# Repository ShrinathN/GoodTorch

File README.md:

# GoodTorch
An STM32G0 based torch for a 20W LED

# Summary
* STM32G0 MCU
* Boost converter (can operate in async or synchronous boost, depending on component placement)
* TP4056 based li-ion charging circuitry (1A max)
* USB-C for charging
* IR2104 gate driver (optional, if synchronous boost has to be used)

# Pics

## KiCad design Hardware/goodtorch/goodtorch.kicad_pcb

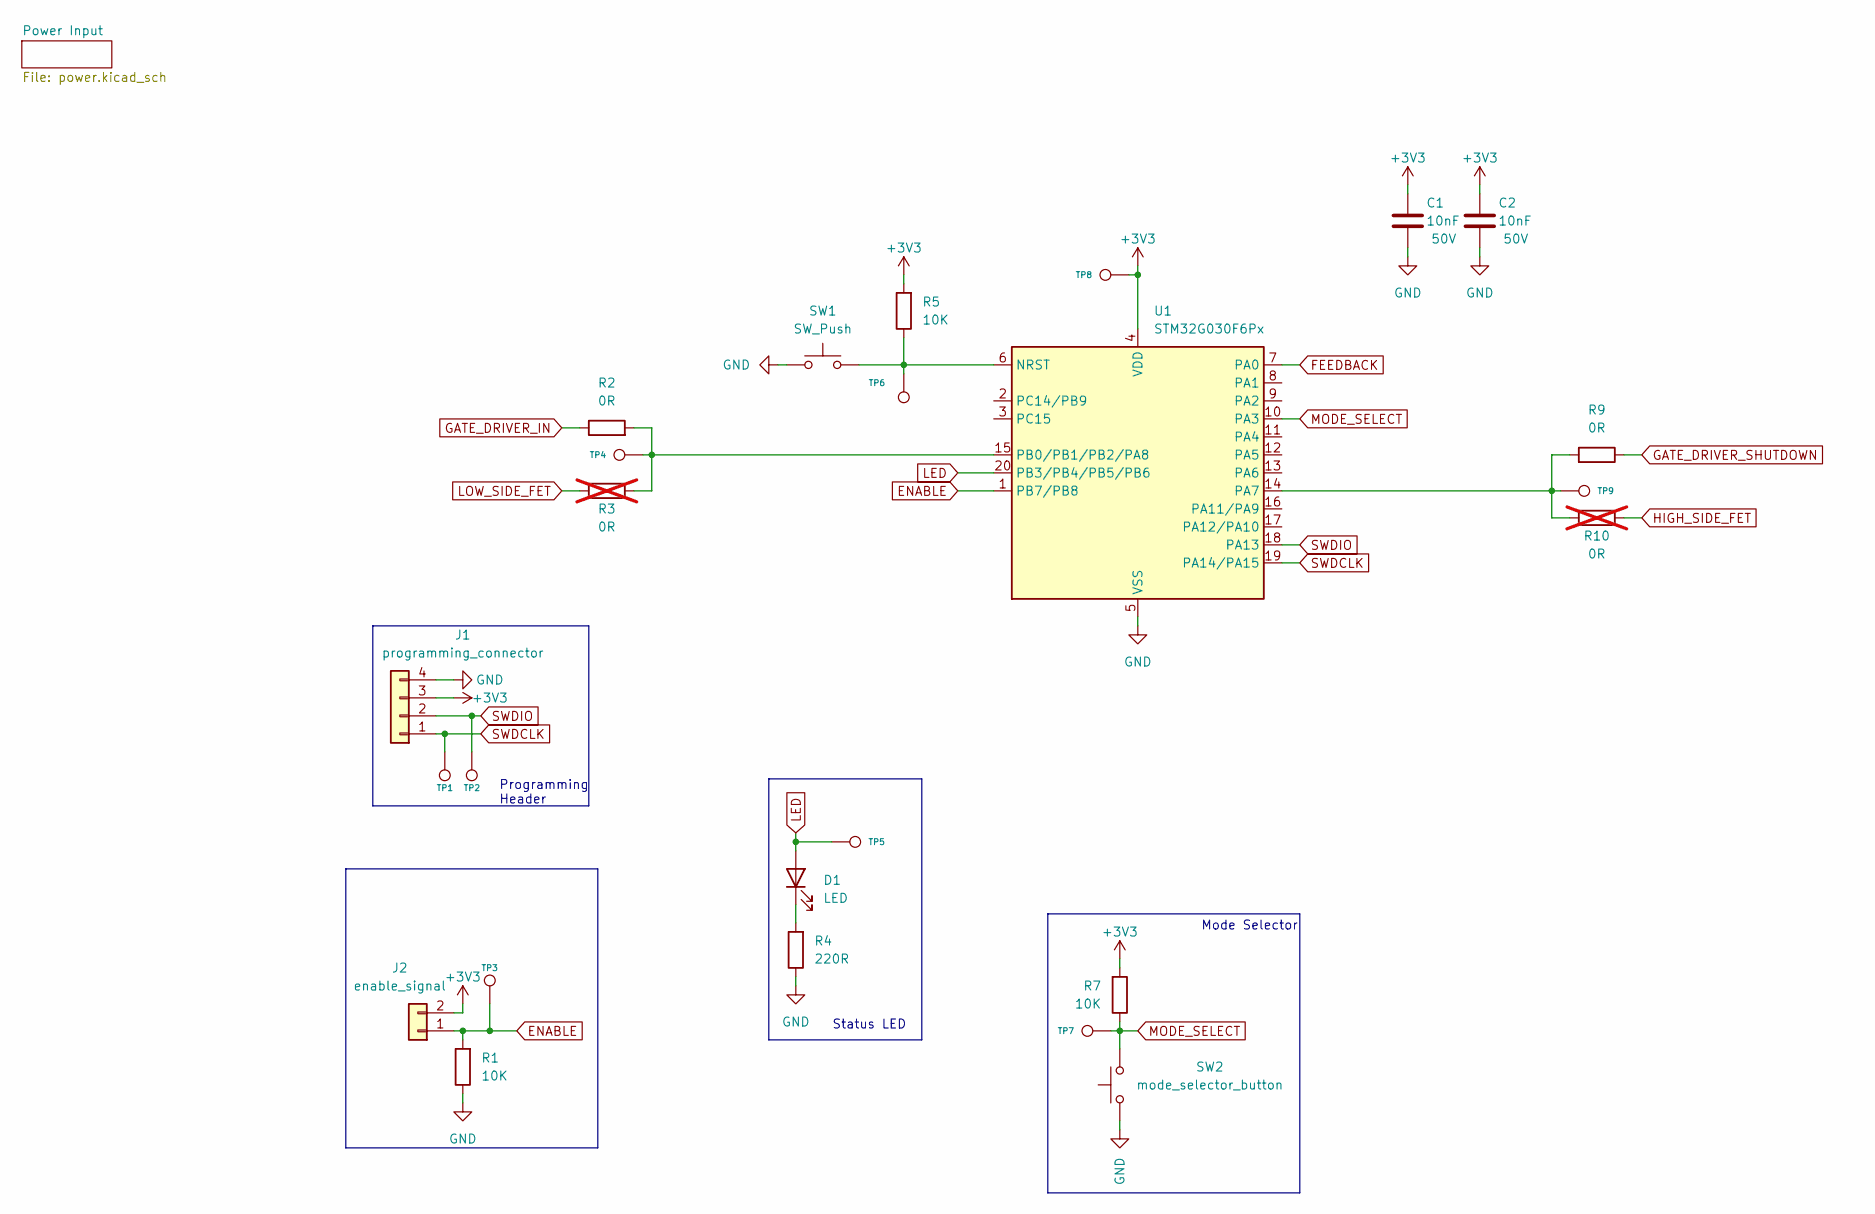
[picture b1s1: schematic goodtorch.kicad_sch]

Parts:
C1, C2: 10nF; C_0805_2012Metric; Rating 50V
D1: LED; LED_1206_3216Metric
J1: programming_connector; PinHeader_1x04_P2.54mm_Vertical
J2: enable_signal; PinHeader_1x02_P2.54mm_Vertical
R1, R5, R7: 10K; R_1206_3216Metric
R2, R9: 0R; R_1206_3216Metric
R3, R10: 0R; R_1206_3216Metric; not fitted
R4: 220R; R_1206_3216Metric
SW1: SW_Push; SW_SPST_TL3342
SW2: mode_selector_button; SW_SPST_TL3342
TP1, TP2, TP3, TP4, TP5, TP6, TP7, TP8, TP9: TestPoint; TestPoint_Pad_D1.0mm
U1: STM32G030F6Px; TSSOP-20_4.4x6.5mm_P0.65mm

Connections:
+3V3: C1.1, C2.1, J1.3, J2.2, R5.2, R7.2, TP8.1, U1.4 (VDD); also elsewhere on the board
BAT_N: C1.2, C2.2, J1.4, R1.1, R4.1, SW1.1, SW2.1, U1.5 (VSS); also elsewhere on the board
ENABLE: J2.1, R1.2, TP3.1, U1.1 (PB7/PB8)
FEEDBACK: U1.7 (PA0); also elsewhere on the board
GATE_DRIVER_IN: R2.1; also elsewhere on the board
GATE_DRIVER_SHUTDOWN: R9.1; also elsewhere on the board
HIGH_SIDE_FET: R10.1; also elsewhere on the board
LED: D1.2 (A), TP5.1, U1.20 (PB3/PB4/PB5/PB6)
LOW_SIDE_FET: R3.1; also elsewhere on the board
MODE_SELECT: R7.1, SW2.2, TP7.1, U1.10 (PA3)
unnamed: D1.1 (K), R4.2
unnamed: R5.1, SW1.2, TP6.1, U1.6 (NRST)
unnamed: R9.2, R10.2, TP9.1, U1.14 (PA7)
unnamed: R2.2, R3.2, TP4.1, U1.15 (PB0/PB1/PB2/PA8)
SWDCLK: J1.1, TP1.1, U1.19 (PA14/PA15)
SWDIO: J1.2, TP2.1, U1.18 (PA13)

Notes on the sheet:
Status LED
Programming Header
Mode Selector

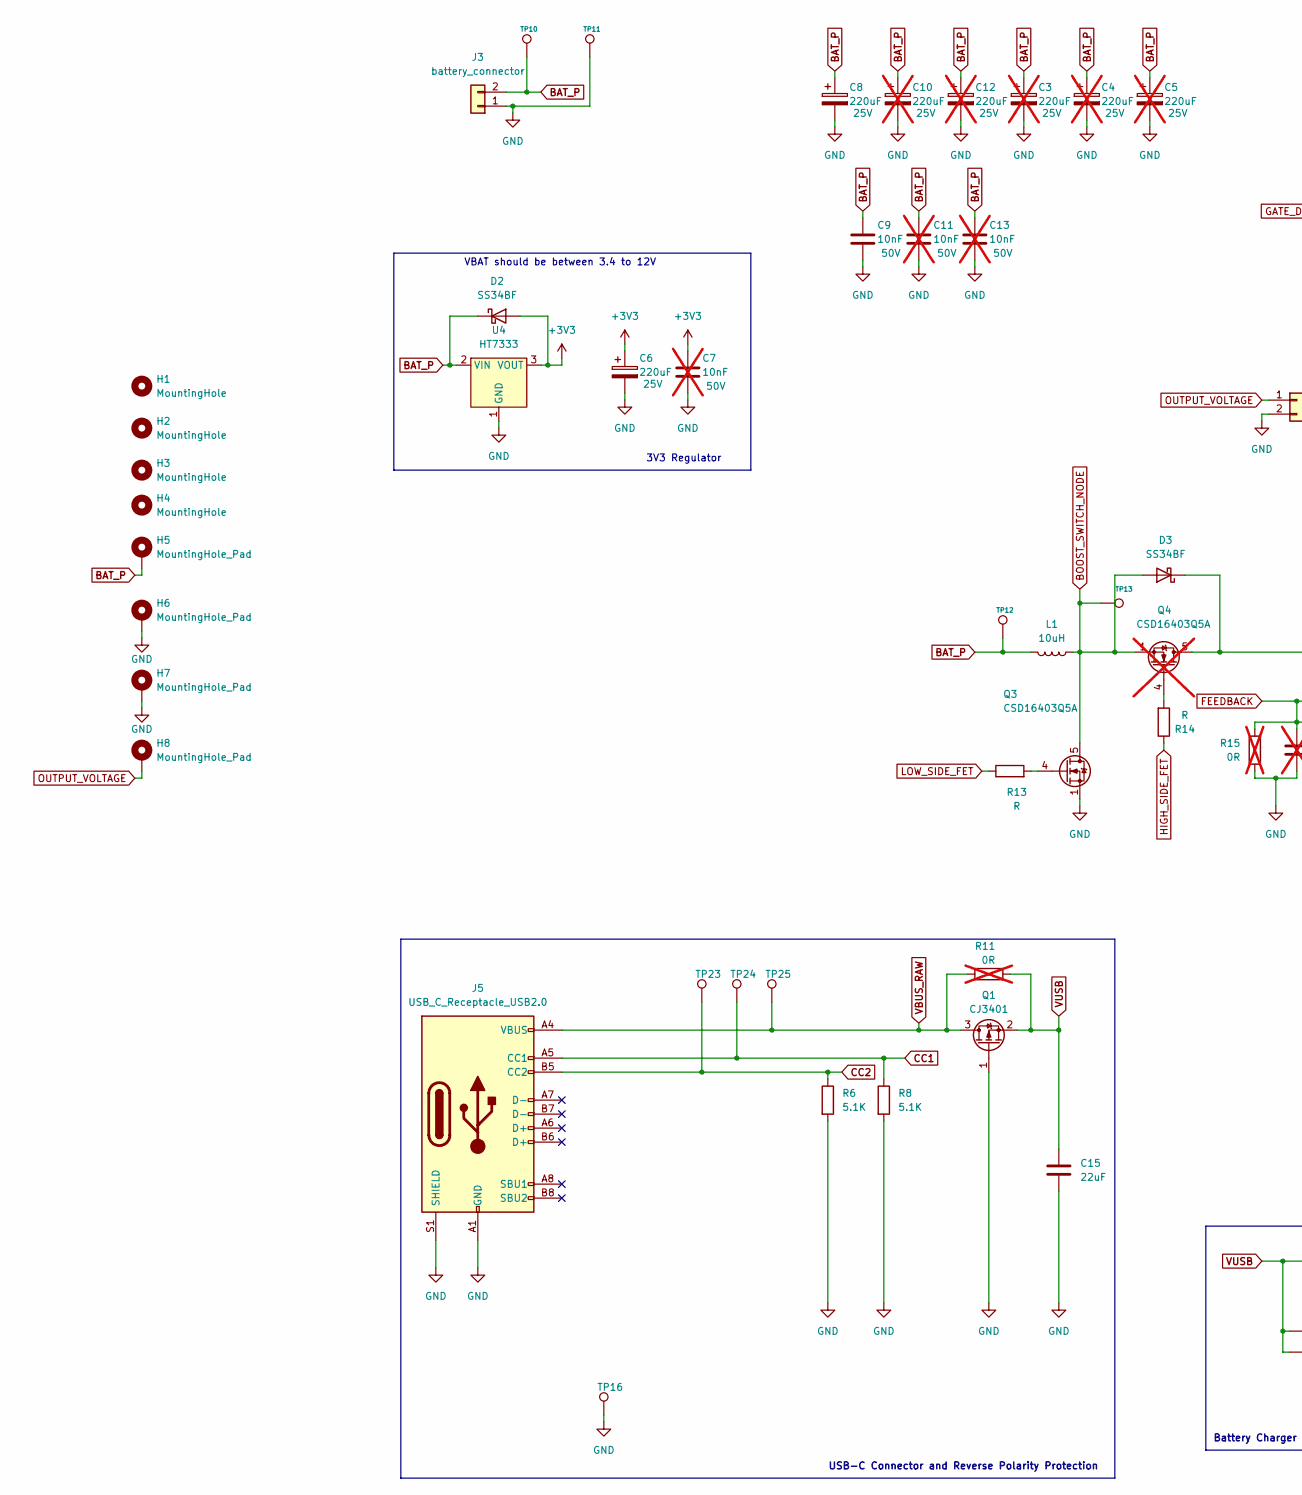
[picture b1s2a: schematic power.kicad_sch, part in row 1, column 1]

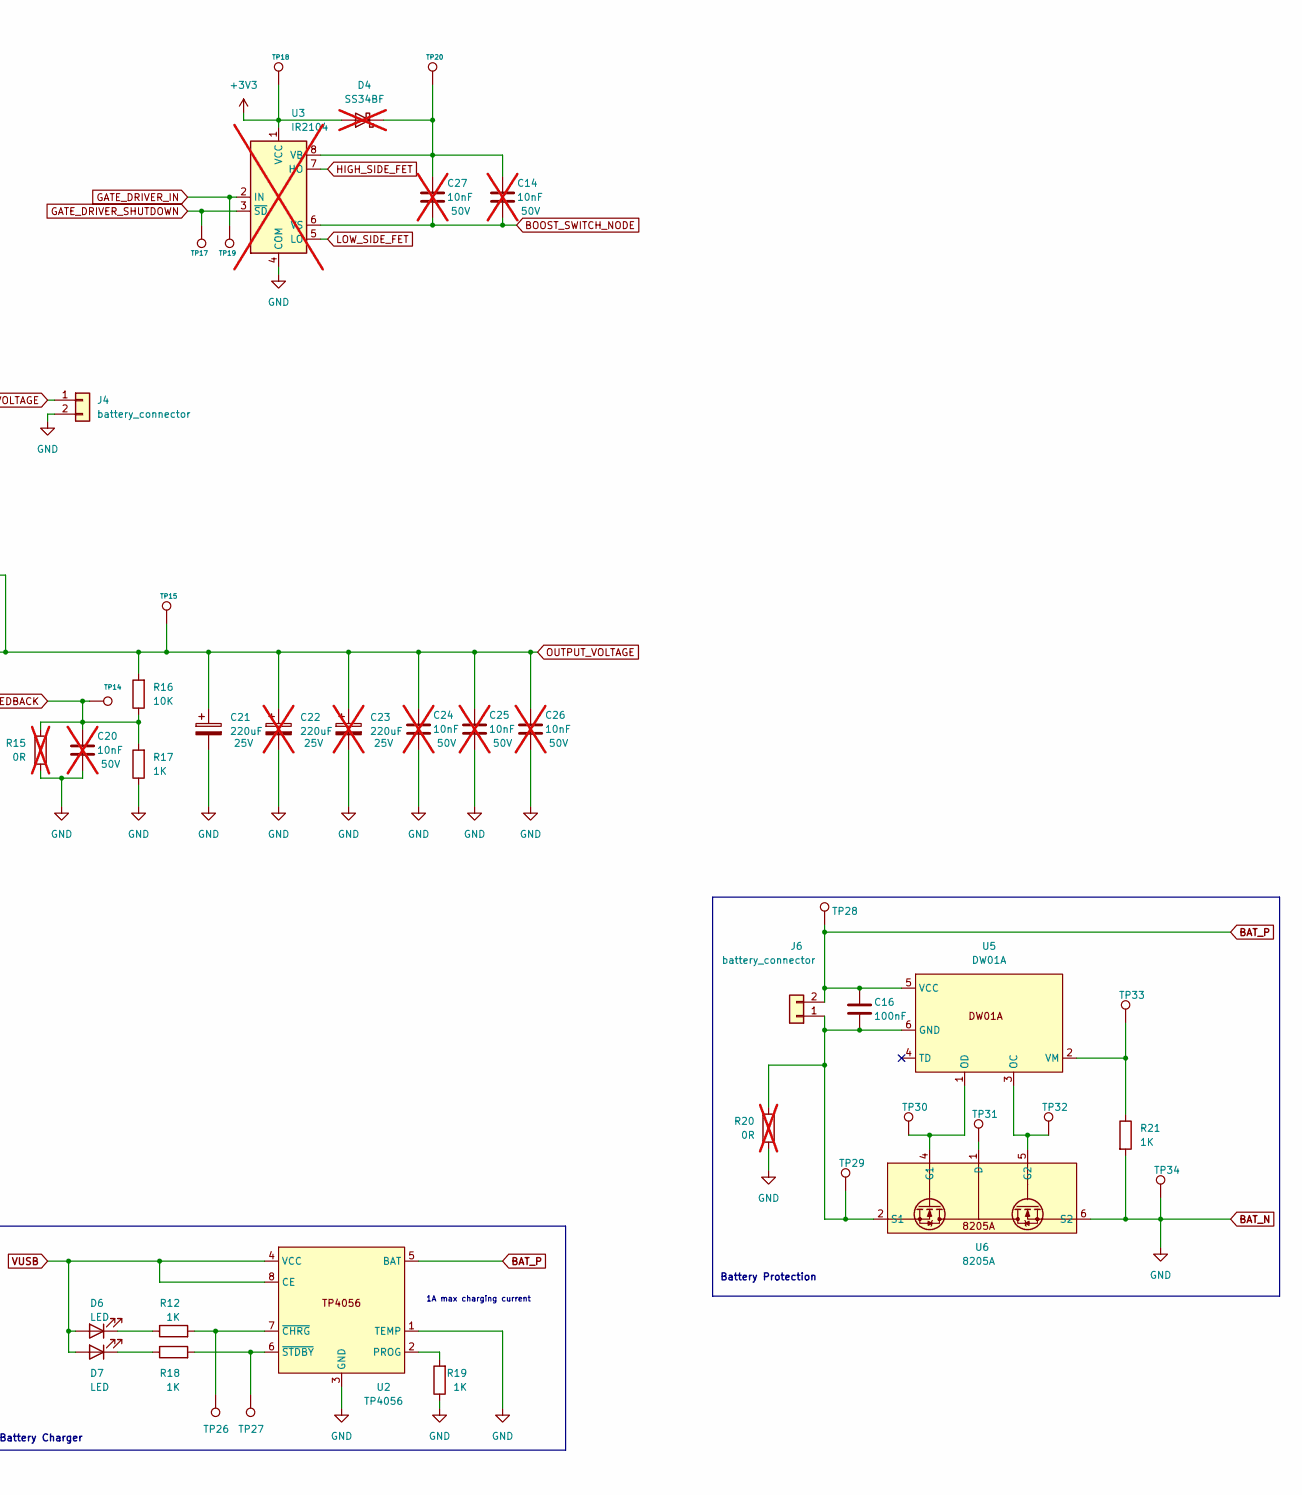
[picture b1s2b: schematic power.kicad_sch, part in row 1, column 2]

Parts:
C3, C4, C5, C10, C12, C22, C23: 220uF; CP_Radial_D5.0mm_P2.00mm; Rating 25V; not fitted
C6, C8, C21: 220uF; CP_Radial_D5.0mm_P2.00mm; Rating 25V
C7, C11, C13, C20, C24, C25, C26, C27: 10nF; C_0805_2012Metric; Rating 50V; not fitted
C9: 10nF; C_0805_2012Metric; Rating 50V
C14: 10nF; C_1206_3216Metric; Rating 50V; not fitted
C15: 22uF; C_0805_2012Metric
C16: 100nF; C_0805_2012Metric
D2, D3: SS34BF; D_SMA; Rating 40V 3A
D4: SS34BF; D_SMA; Rating 40V 3A; not fitted
D6, D7: LED; LED_1206_3216Metric_Pad1.42x1.75mm_HandSolder
H1, H2, H3, H4: MountingHole; MountingHole_3.2mm_M3
H5, H6, H7, H8: MountingHole_Pad; MountingHole_2.2mm_M2_DIN965_Pad
J3, J4: battery_connector; TerminalBlock_Phoenix_MPT-0,5-2-2.54_1x02_P2.54mm_Horizontal
J5: USB_C_Receptacle_USB2.0; USB_C_Receptacle_XKB_U262-16XN-4BVC11
J6: battery_connector; PinHeader_1x02_P2.54mm_Horizontal
L1: 10uH; L_Bourns_SRR1208_12.7x12.7mm
Q1: CJ3401; SOT-23
Q3: CSD16403Q5A; TDSON-8-1
Q4: CSD16403Q5A; TDSON-8-1; not fitted
R6, R8: 5.1K; R_0805_2012Metric
R11, R20: 0R; R_0805_2012Metric; not fitted
R12, R18, R19, R21: 1K; R_0805_2012Metric
R13, R14: R; R_1206_3216Metric
R15: 0R; R_1206_3216Metric; not fitted
R16: 10K; R_1206_3216Metric
R17: 1K; R_1206_3216Metric
TP10, TP11, TP12, TP13, TP14, TP15, TP16, TP17, TP18, TP19, TP20, TP23, TP24, TP25, TP26, TP27, TP28, TP29, TP30, TP31, TP32, TP33, TP34: TestPoint; TestPoint_Pad_D1.0mm
U2: TP4056; SOP-8_3.9x4.9mm_P1.27mm
U3: IR2104; SOIC-8_3.9x4.9mm_P1.27mm; not fitted
U4: HT7333; SOT-89-3
U5: DW01A; SOT-23-6
U6: 8205A; TSSOP-8_4.4x3mm_P0.65mm

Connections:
+3V3: C6.1, C7.1, D2.2 (A), D4.2 (A), TP18.1, U3.1 (VCC), U4.3 (VOUT); also elsewhere on the board
BAT_N: C3.2, C4.2, C5.2, C6.2, C7.2, C8.2, C9.2, C10.2, C11.2, C12.2, C13.2, C15.2, C20.2, C21.2, C22.2, C23.2, C24.2, C25.2, C26.2, H6.1, H7.1, J3.1, J4.2, J5.A1 (GND), J5.A12 (GND), J5.B1 (GND), J5.B12 (GND), J5.S1 (SHIELD), Q1.1 (G), Q3.1 (S), Q3.2 (S), Q3.3 (S), R6.2, R8.2, R15.2, R17.1, R19.1, R20.1, R21.2, TP11.1, TP16.1, TP34.1, U2.1 (TEMP), U2.3 (GND), U3.4 (COM), U4.1 (GND), U6.6 (S2), U6.7 (S2); also elsewhere on the board
BAT_P: C3.1, C4.1, C5.1, C8.1, C9.1, C10.1, C11.1, C12.1, C13.1, C16.1, D2.1 (K), H5.1, J3.2, J6.2, L1.2, TP10.1, TP12.1, TP28.1, U2.5 (BAT), U4.2 (VIN), U5.5 (VCC)
BOOST_SWITCH_NODE: C14.2, C27.2, D3.2 (A), L1.1, Q3.5 (D), Q4.1 (S), Q4.2 (S), Q4.3 (S), TP13.1, U3.6 (VS)
CC1: J5.A5 (CC1), R8.1, TP24.1
CC2: J5.B5 (CC2), R6.1, TP23.1
FEEDBACK: C20.1, R15.1, R16.1, R17.2, TP14.1; also elsewhere on the board
GATE_DRIVER_IN: TP19.1, U3.2 (IN); also elsewhere on the board
GATE_DRIVER_SHUTDOWN: TP17.1, U3.3 (~SD); also elsewhere on the board
HIGH_SIDE_FET: R14.1, U3.7 (HO); also elsewhere on the board
LOW_SIDE_FET: R13.1, U3.5 (LO); also elsewhere on the board
unnamed: C14.1, C27.1, D4.1 (K), TP20.1, U3.8 (VB)
unnamed: D6.1 (K), R12.1
unnamed: D7.1 (K), R18.1
unnamed: C16.2, J6.1, R20.2, TP29.1, U5.6 (GND), U6.2 (S1), U6.3 (S1)
unnamed: Q3.4 (G), R13.2
unnamed: Q4.4 (G), R14.2
unnamed: TP31.1, U6.1 (D), U6.8 (D)
unnamed: R19.2, U2.2 (PROG)
unnamed: R12.2, TP26.1, U2.7 (~CHRG)
unnamed: R18.2, TP27.1, U2.6 (~STDBY)
unnamed: TP32.1, U5.3 (OC), U6.5 (G2)
unnamed: TP30.1, U5.1 (OD), U6.4 (G1)
unnamed: R21.1, TP33.1, U5.2 (VM)
OUTPUT_VOLTAGE: C21.1, C22.1, C23.1, C24.1, C25.1, C26.1, D3.1 (K), H8.1, J4.1, Q4.5 (D), R16.2, TP15.1
VBUS_RAW: J5.A4 (VBUS), J5.A9 (VBUS), J5.B4 (VBUS), J5.B9 (VBUS), Q1.3 (D), R11.1, TP25.1
VUSB: C15.1, D6.2 (A), D7.2 (A), Q1.2 (S), R11.2, U2.4 (VCC), U2.8 (CE)

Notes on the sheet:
Battery Protection
VBAT should be between 3.4 to 12V
3V3 Regulator
1A max charging current
USB-C Connector and Reverse Polarity Protection
Battery Charger

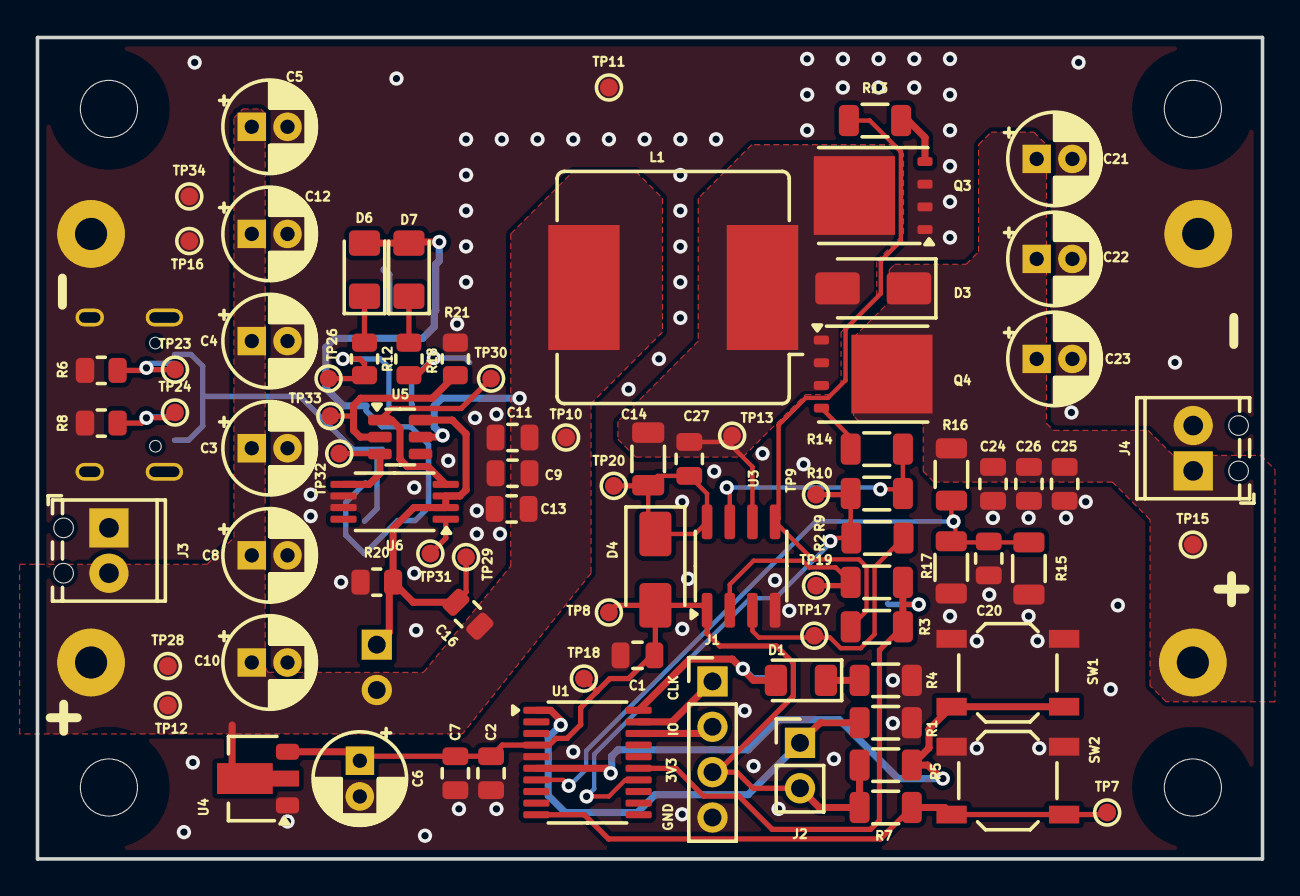
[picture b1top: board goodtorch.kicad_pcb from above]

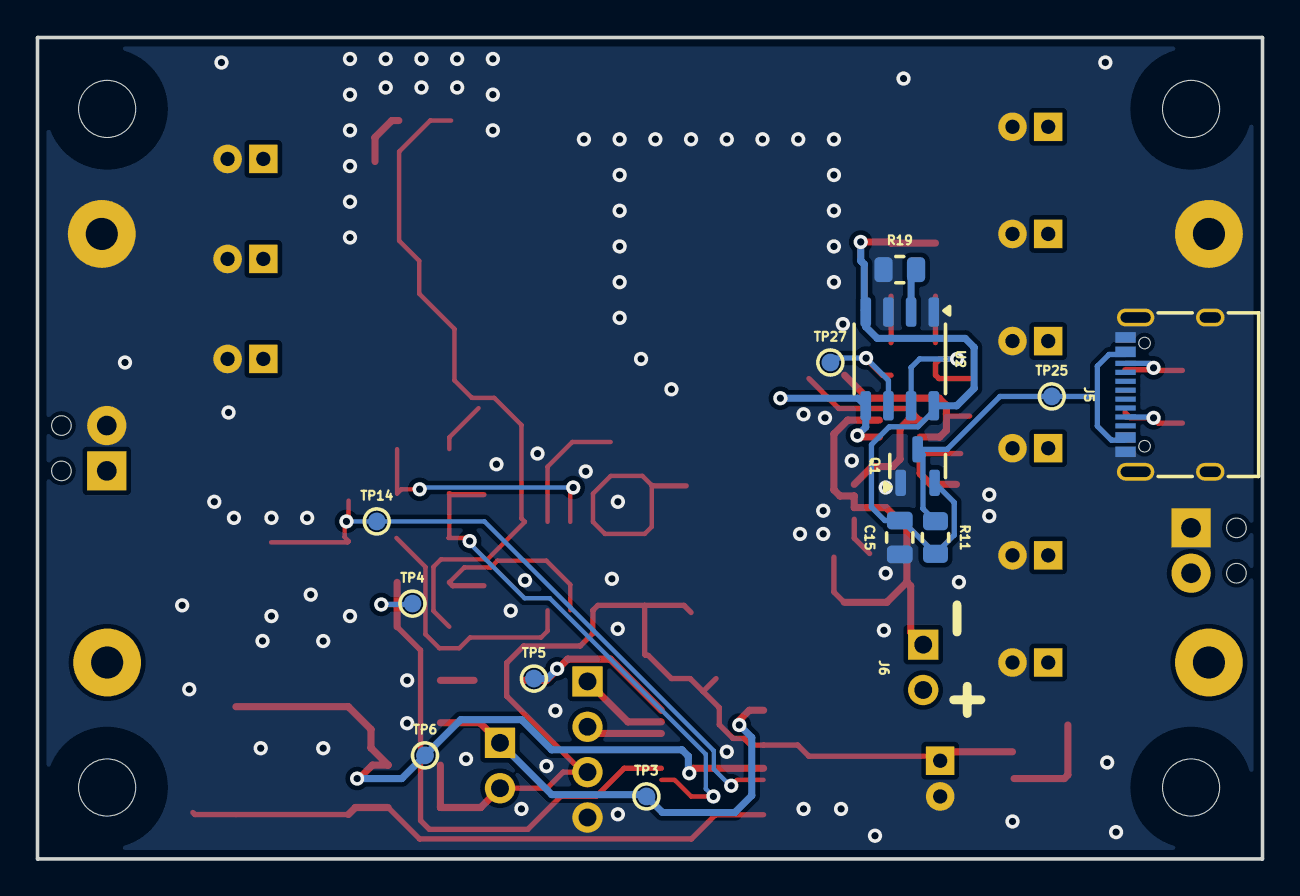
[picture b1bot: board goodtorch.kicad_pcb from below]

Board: 2 copper layers, 68.6 x 46.0 mm, 106 parts (14 on the bottom side), 36 nets.

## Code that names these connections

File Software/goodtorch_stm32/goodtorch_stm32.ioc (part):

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Mcu.Name=STM32G030F6Px
Mcu.Package=TSSOP20
Mcu.UserName=STM32G030F6Px
PA0.Mode=IN0
PA0.Signal=ADC1_IN0
PA13.Mode=Serial_Wire
PA13.Signal=SYS_SWDIO
PA14-BOOT0.Mode=Serial_Wire
PA14-BOOT0.Signal=SYS_SWCLK
PA14-BOOT0__PA15.StandardMode=true
PA3.GPIOParameters=GPIO_Label
PA3.GPIO_Label=MODE_SELECT
PA3.Signal=GPXTI3
PA8.Signal=S_TIM1_CH1
PB0__PB1__PB2__PA8.StandardMode=true
PB3.GPIOParameters=GPIO_Speed,PinState,GPIO_Label
PB3.GPIO_Label=LED
PB3.GPIO_Speed=GPIO_SPEED_FREQ_HIGH
PB3.PinState=GPIO_PIN_SET
PB3.Signal=GPIO_Output
PB3__PB4__PB5__PB6.StandardMode=true
PB7.GPIOParameters=GPIO_Label
PB7.GPIO_Label=ENABLE
PB7.Signal=GPIO_Input
PB7__PB8.StandardMode=true
PC14-OSC32_IN\ (PC14)__PB9.StandardMode=true
RCC.HSE_VALUE=8000000
RCC.SYSCLKFreq_VALUE=64000000
RCC.SYSCLKSource=RCC_SYSCLKSOURCE_PLLCLK
board=custom

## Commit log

2024-07-28 Added files
